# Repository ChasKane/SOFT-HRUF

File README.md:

# SOFT-HRUF
This is the github page for the electronics company SoftHRUF run by Ecca Scott Urueta.
A strong contributer, ChasKane (YoungSage) designed the PCB for the company's custom
stenography keyboard.

This most recent version of the keyboard integrates a microcontroller (Atmega32U4-AU)
onto the PCB, and is split at the middle, connected by a 10p10c wire (ethernet but with 10
wires).

## Current work
Current design is in the `/Split Corded/` folder.

## Future work
We're currently contracting on a more streamlined version with bluetooth, micro SD slot, and USB-C. Contact us for more updates!

## Contact
Please direct any questions about the electronics on the Split Corded keyboard to ChasKane `LawrenceCKane@gmail.com`.
For all other questions, comments, etc. please email Scott `ecca@softhruf.love`.

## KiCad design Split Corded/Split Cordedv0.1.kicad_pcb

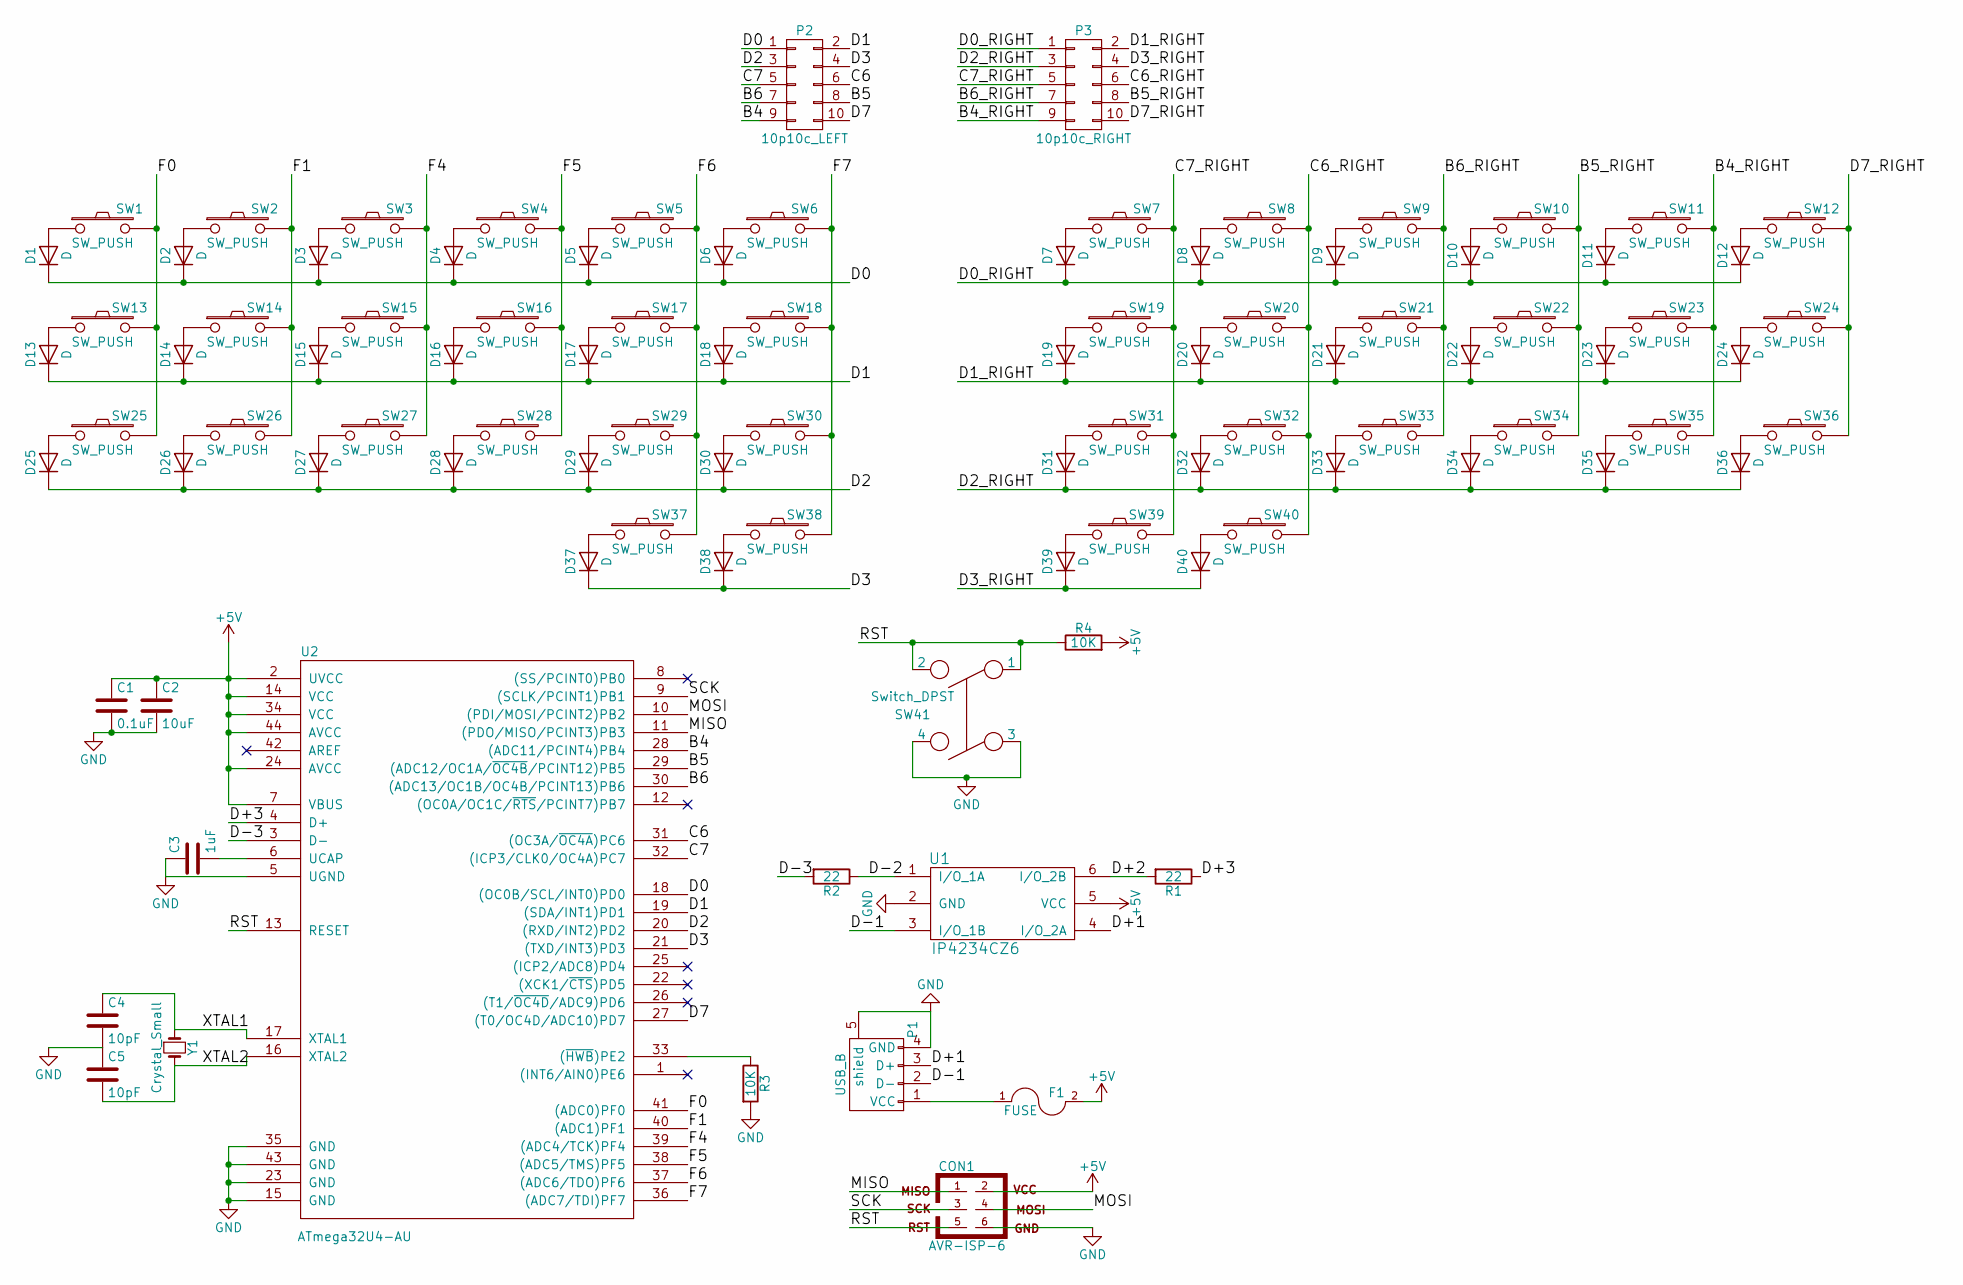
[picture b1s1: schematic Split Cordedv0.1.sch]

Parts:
C1: 0.1uF; C_0603
C2: 10uF; C_0603
C3: 1uF; C_0603
C4, C5: 10pF; C_0402
CON1: AVR-ISP-6; Pin_Header_Straight_2x03
D1, D2, D3, D4, D5, D6, D7, D8, D9, D10, D11, D12, D13, D14, D15, D16, D17, D18, D19, D20, D21, D22, D23, D24, D25, D26, D27, D28, D29, D30, D31, D32, D33, D34, D35, D36, D37, D38, D39, D40: D; MiniMELF_Standard
F1: FUSE; Fuse_MF-MSMF050-2
P1: USB_B; USB_Micro-B
P2: 10p10c_LEFT; 10p10c
P3: 10p10c_RIGHT; 10p10c
R1, R2: 22; R_0603
R3, R4: 10K; R_0603
SW1, SW2, SW3, SW4, SW5, SW6, SW7, SW8, SW9, SW10, SW11, SW12, SW13, SW14, SW15, SW16, SW17, SW18, SW19, SW20, SW21, SW22, SW23, SW24, SW25, SW26, SW27, SW28, SW29, SW30, SW31, SW32, SW33, SW34, SW35, SW36, SW37, SW38, SW39, SW40: SW_PUSH; SW_Matias_Quiet_With_Mounting_Hole_Frame
SW41: Switch_DPST; SMD_Button_DTSM_62K_S_V_T
U1: IP4234CZ6; SOT457
U2: ATmega32U4-AU; TQFP-44_10x10mm_Pitch0.8mm
Y1: Crystal_Small; SMD_5.0x3.2_X053201602002

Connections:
+5V: C1.1, C2.1, CON1.2, F1.2, R4.2, U1.5 (VCC), U2.2 (UVCC), U2.7 (VBUS), U2.14 (VCC), U2.24 (AVCC), U2.34 (VCC), U2.44 (AVCC)
/B4: P2.9, U2.28 ((ADC11/PCINT4)PB4)
/B4_RIGHT: P3.9, SW11.2, SW23.2, SW35.2
/B5: P2.8, U2.29 ((ADC12/OC1A/~OC4B~/PCINT12)PB5)
/B5_RIGHT: P3.8, SW10.2, SW22.2, SW34.2
/B6: P2.7, U2.30 ((ADC13/OC1B/OC4B/PCINT13)PB6)
/B6_RIGHT: P3.7, SW9.2, SW21.2, SW33.2
/C6: P2.6, U2.31 ((OC3A/~OC4A~)PC6)
/C6_RIGHT: P3.6, SW8.2, SW20.2, SW32.2, SW40.2
/C7: P2.5, U2.32 ((ICP3/CLK0/OC4A)PC7)
/C7_RIGHT: P3.5, SW7.2, SW19.2, SW31.2, SW39.2
/D0: D1.1 (K), D2.1 (K), D3.1 (K), D4.1 (K), D5.1 (K), D6.1 (K), P2.1, U2.18 ((OC0B/SCL/INT0)PD0)
/D0_RIGHT: D7.1 (K), D8.1 (K), D9.1 (K), D10.1 (K), D11.1 (K), D12.1 (K), P3.1
/D1: D13.1 (K), D14.1 (K), D15.1 (K), D16.1 (K), D17.1 (K), D18.1 (K), P2.2, U2.19 ((SDA/INT1)PD1)
/D1_RIGHT: D19.1 (K), D20.1 (K), D21.1 (K), D22.1 (K), D23.1 (K), D24.1 (K), P3.2
/D2: D25.1 (K), D26.1 (K), D27.1 (K), D28.1 (K), D29.1 (K), D30.1 (K), P2.3, U2.20 ((RXD/INT2)PD2)
/D2_RIGHT: D31.1 (K), D32.1 (K), D33.1 (K), D34.1 (K), D35.1 (K), D36.1 (K), P3.3
/D3: D37.1 (K), D38.1 (K), P2.4, U2.21 ((TXD/INT3)PD3)
/D3_RIGHT: D39.1 (K), D40.1 (K), P3.4
/D7: P2.10, U2.27 ((T0/OC4D/ADC10)PD7)
/D7_RIGHT: P3.10, SW12.2, SW24.2, SW36.2
/D+1: P1.3 (D+), U1.4 (I/O_2A)
/D+2: R1.2, U1.6 (I/O_2B)
/D+3: R1.1, U2.4 (D+)
/D-1: P1.2 (D-), U1.3 (I/O_1B)
/D-2: R2.1, U1.1 (I/O_1A)
/D-3: R2.2, U2.3 (D-)
/F0: SW1.2, SW13.2, SW25.2, U2.41 ((ADC0)PF0)
/F1: SW2.2, SW14.2, SW26.2, U2.40 ((ADC1)PF1)
/F4: SW3.2, SW15.2, SW27.2, U2.39 ((ADC4/TCK)PF4)
/F5: SW4.2, SW16.2, SW28.2, U2.38 ((ADC5/TMS)PF5)
/F6: SW5.2, SW17.2, SW29.2, SW37.2, U2.37 ((ADC6/TDO)PF6)
/F7: SW6.2, SW18.2, SW30.2, SW38.2, U2.36 ((ADC7/TDI)PF7)
/MISO: CON1.1, U2.11 ((PDO/MISO/PCINT3)PB3)
/MOSI: CON1.4, U2.10 ((PDI/MOSI/PCINT2)PB2)
/RST: CON1.5, R4.1, SW41.1, SW41.2, U2.13 (RESET)
/SCK: CON1.3, U2.9 ((SCLK/PCINT1)PB1)
/XTAL1: C4.1, U2.17 (XTAL1), Y1.1
unnamed: C3.2, U2.6 (UCAP)
unnamed: D1.2 (A), SW1.1
unnamed: D2.2 (A), SW2.1
unnamed: D3.2 (A), SW3.1
unnamed: D4.2 (A), SW4.1
unnamed: D5.2 (A), SW5.1
unnamed: D6.2 (A), SW6.1
unnamed: D7.2 (A), SW7.1
unnamed: D8.2 (A), SW8.1
unnamed: D9.2 (A), SW9.1
unnamed: D10.2 (A), SW10.1
unnamed: D11.2 (A), SW11.1
unnamed: D12.2 (A), SW12.1
unnamed: D13.2 (A), SW13.1
unnamed: D14.2 (A), SW14.1
unnamed: D15.2 (A), SW15.1
unnamed: D16.2 (A), SW16.1
unnamed: D17.2 (A), SW17.1
unnamed: D18.2 (A), SW18.1
unnamed: D19.2 (A), SW19.1
unnamed: D20.2 (A), SW20.1
unnamed: D21.2 (A), SW21.1
unnamed: D22.2 (A), SW22.1
unnamed: D23.2 (A), SW23.1
unnamed: D24.2 (A), SW24.1
unnamed: D25.2 (A), SW25.1
unnamed: D26.2 (A), SW26.1
unnamed: D27.2 (A), SW27.1
unnamed: D28.2 (A), SW28.1
unnamed: D29.2 (A), SW29.1
unnamed: D30.2 (A), SW30.1
unnamed: D31.2 (A), SW31.1
unnamed: D32.2 (A), SW32.1
unnamed: D33.2 (A), SW33.1
unnamed: D34.2 (A), SW34.1
unnamed: D35.2 (A), SW35.1
unnamed: D36.2 (A), SW36.1
unnamed: D37.2 (A), SW37.1
unnamed: D38.2 (A), SW38.1
unnamed: D39.2 (A), SW39.1
unnamed: D40.2 (A), SW40.1
unnamed: F1.1, P1.1 (VCC)
unnamed: R3.1, U2.33 ((~HWB~)PE2)

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
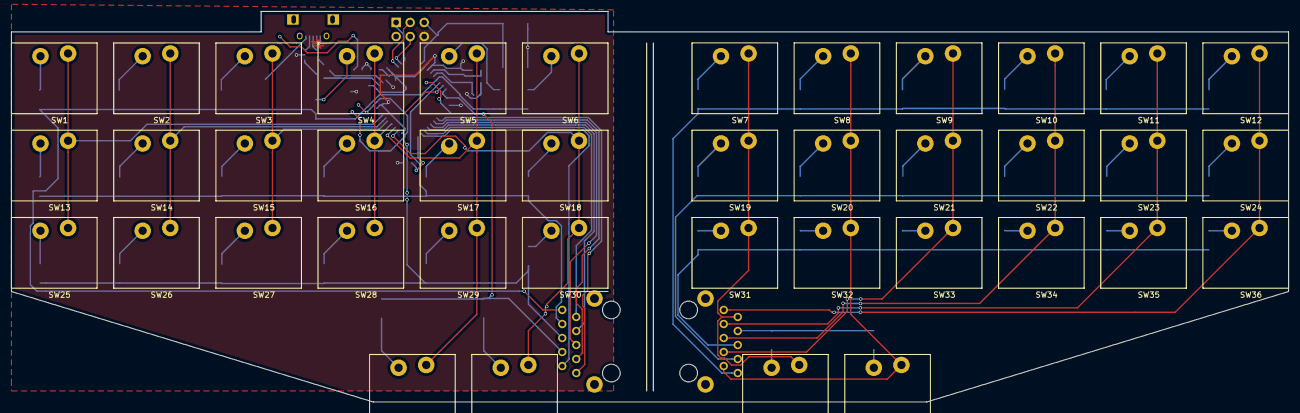
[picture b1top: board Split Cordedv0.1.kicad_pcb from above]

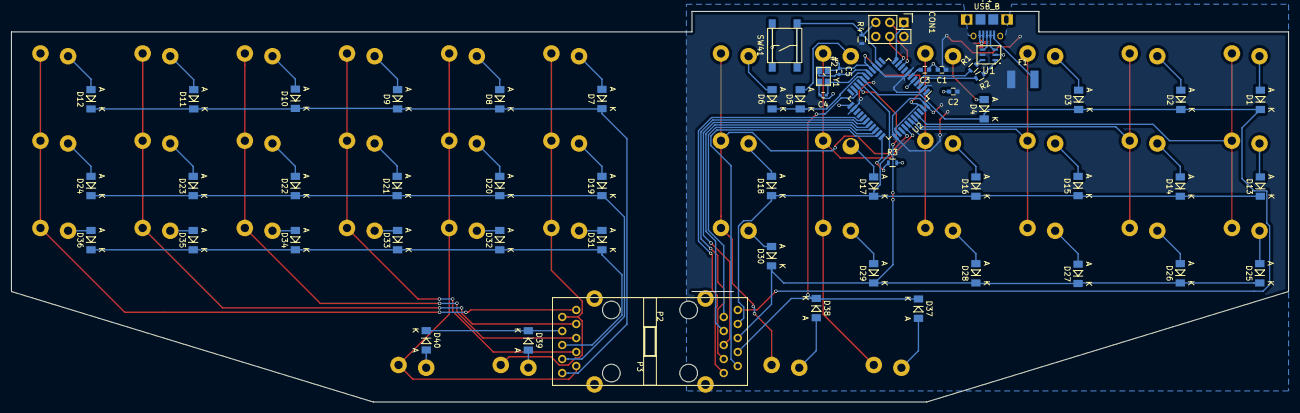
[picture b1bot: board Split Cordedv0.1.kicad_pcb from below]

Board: 2 copper layers, 231.2 x 70.7 mm, 98 parts (58 on the bottom side), 83 nets.

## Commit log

2017-03-11 Split Keyboard
    This is everything to date; future updates will be made using GitHub,
    such as the possible bluetooth version.
2017-03-12 test
2017-03-28 Still trying to get the moved interconnect back
2017-03-28 Should be good now
    Apparently, I had the most updated files on my external. Now everything
    is in one place!
2017-03-28 All connections checked, all ground and VCC connections specifically. Awaiting final tests in the lab on current prototype before finalizing.
2017-03-30 In the middle of making last few changes. Last thing I need to do is fiddle with the USB connector, since the first one showed signs of weakness.
2017-06-06 pushing everything to github for the summer -- I won't have time to work on this :/
